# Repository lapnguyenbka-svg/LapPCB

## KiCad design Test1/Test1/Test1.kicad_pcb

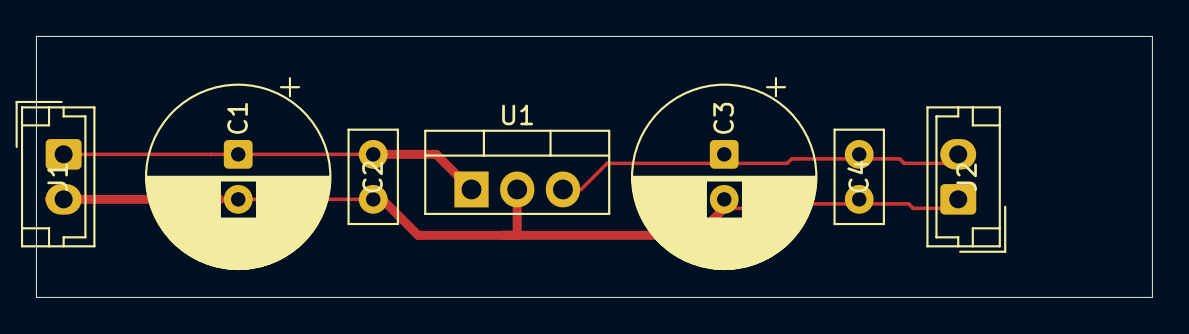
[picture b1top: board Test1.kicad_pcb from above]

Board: 4 copper layers, 62.0 x 14.5 mm, 7 parts (0 on the bottom side), 3 nets.

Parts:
C1, C3: 1000uF; CP_Radial_D10.0mm_P2.50mm
C2, C4: 104; C_Disc_D5.0mm_W2.5mm_P2.50mm
J1, J2: Conn_01x02_Pin; JST_EH_B2B-EH-A_1x02_P2.50mm_Vertical
U1: LM7805_TO220; TO-220-3_Vertical

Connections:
GND: C1.2, C2.2, C3.2, C4.2, J1.2, J2.1, U1.2 (GND)
unnamed: C1.1, C2.1, J1.1, U1.1 (VI)
unnamed: C3.1, C4.1, J2.2, U1.3 (VO)

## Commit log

2026-01-19 initial pcb version
